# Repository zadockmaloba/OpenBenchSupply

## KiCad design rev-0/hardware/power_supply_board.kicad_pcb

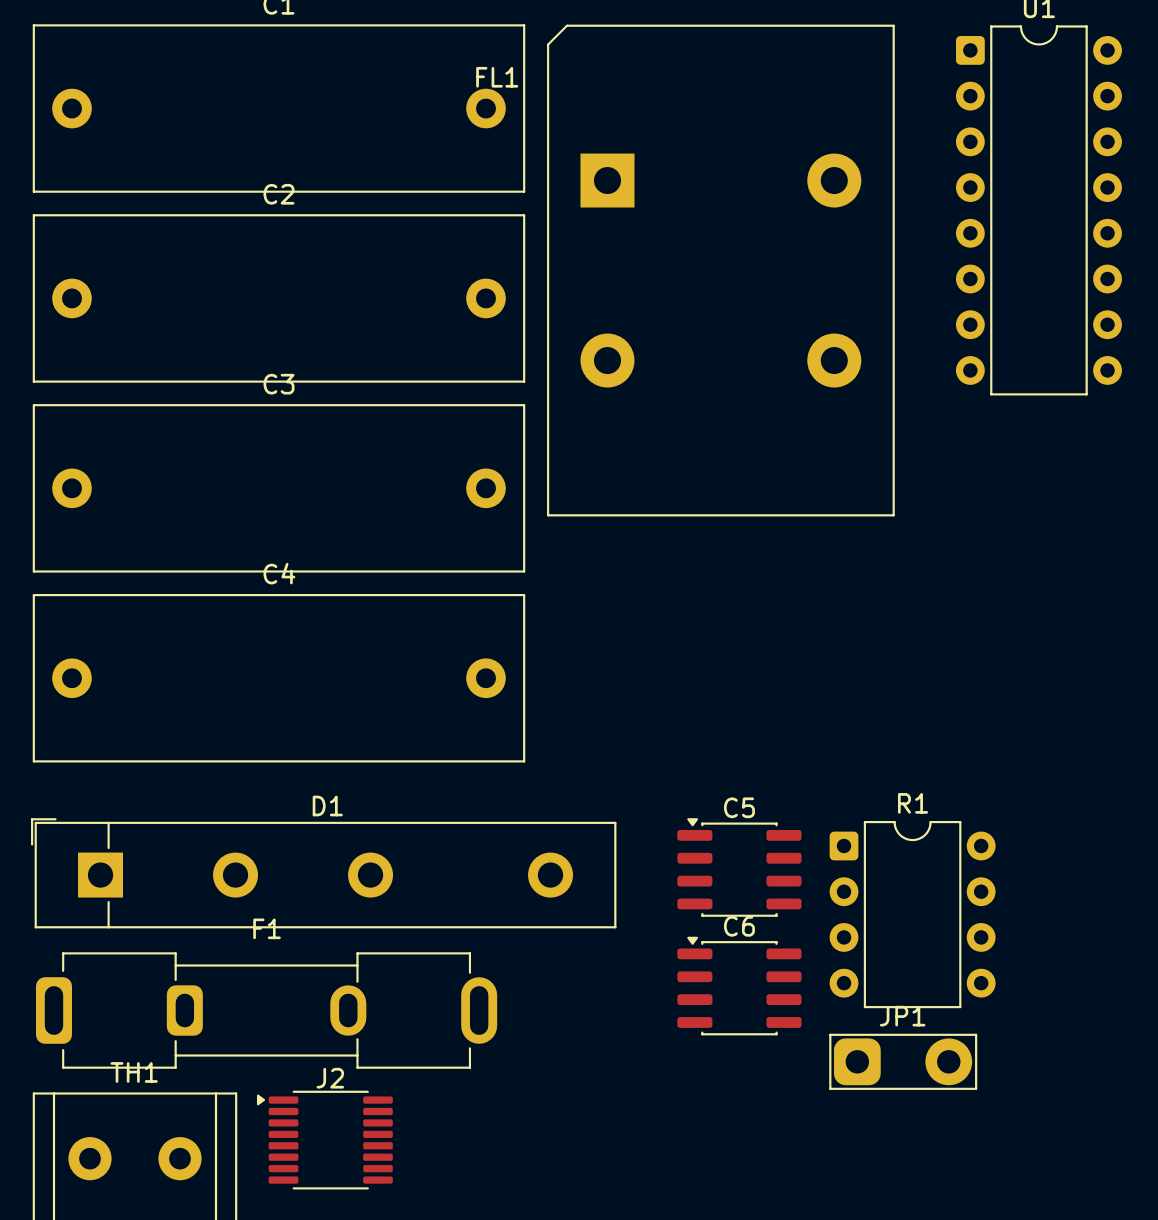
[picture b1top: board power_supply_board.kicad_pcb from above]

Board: 2 copper layers, 14 parts (0 on the bottom side), 10 nets, no tracks yet.

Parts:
C1: 220nF, 250V; C_Rect_L27.0mm_W9.0mm_P23.00mm
C2, C3: 2.2nF, 250V; C_Rect_L27.0mm_W9.0mm_P23.00mm
C4: 1000nF, 275V; C_Rect_L27.0mm_W9.0mm_P23.00mm
C5, C6: 470uF, 250V; SOIC-8_3.9x4.9mm_P1.27mm
D1: B250C3x00-2200A; Diode_Bridge_32.0x5.6x17.0mm_P10.0mm_P7.5mm
F1: 5A; Fuseholder_Clip-5x20mm_Keystone_3512P_Inline_P23.62x7.27mm_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
FL1: PH9455x405NL; L_CommonMode_PulseElectronics_PH9455x405NL_1
J2: 240V AC (LNE); SSOP-16_3.9x4.9mm_P0.635mm
JP1: 110V = Closed; TestPoint_2Pads_Pitch5.08mm_Drill1.3mm
R1: 150K, 1W; DIP-8_W7.62mm
TH1: NTC 5D-9; R_Radial_Power_L11.0mm_W7.0mm_P5.00mm
U1: TL494; DIP-16_W7.62mm

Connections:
/Input Stage/HV DC Filtering/AC_IN: C2.1, C4.1, D1.2, FL1.4, JP1.1 (A)
/Input Stage/HV DC Filtering/IN+: C5.1, D1.4 (+), R1.1
/Input Stage/HV DC Filtering/IN-: C6.2, D1.1 (-)
/Input Stage/Input Filtering/L: C1.1, FL1.1, TH1.2
/Input Stage/Input Filtering/N: C1.2, F1.2, FL1.2
/Input Stage/Input Filtering/N_Filtered: C3.2, C4.2, D1.3, FL1.3
/Input Stage/L: J2.1, TH1.1
/Input Stage/N: F1.1, J2.2
Earth: C2.2, C3.1, J2.3
unnamed: C5.2, C6.1, JP1.2 (B), R1.2
